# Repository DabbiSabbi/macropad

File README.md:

# My-Macropad
- A macropad that uses F13-19
- Has an RGB light bar.
- Has a display
- Has 6 keys and an rotary encoder

The body is in 3 parts, a lid, base and diffuser, The diffuser is meant to be printed in a clear material such as clear PETG. 

# BOM
| Part | Quantity |
| - | - |
| Seeed XIAO RP2040  | 1 |
| 1N4148 Diodes  | 7 |
| MX-Style switches  | 6 |
| EC11E Rotary encoders | 1 |
| 0.91 inch OLED display    | 1 |
| SK6812 MINI-E LEDs | 6 |
| DSA keycaps | 6 |
| M3x16mm screws | 4 |
| M3x5mx4mm heatset inserts | 4 |

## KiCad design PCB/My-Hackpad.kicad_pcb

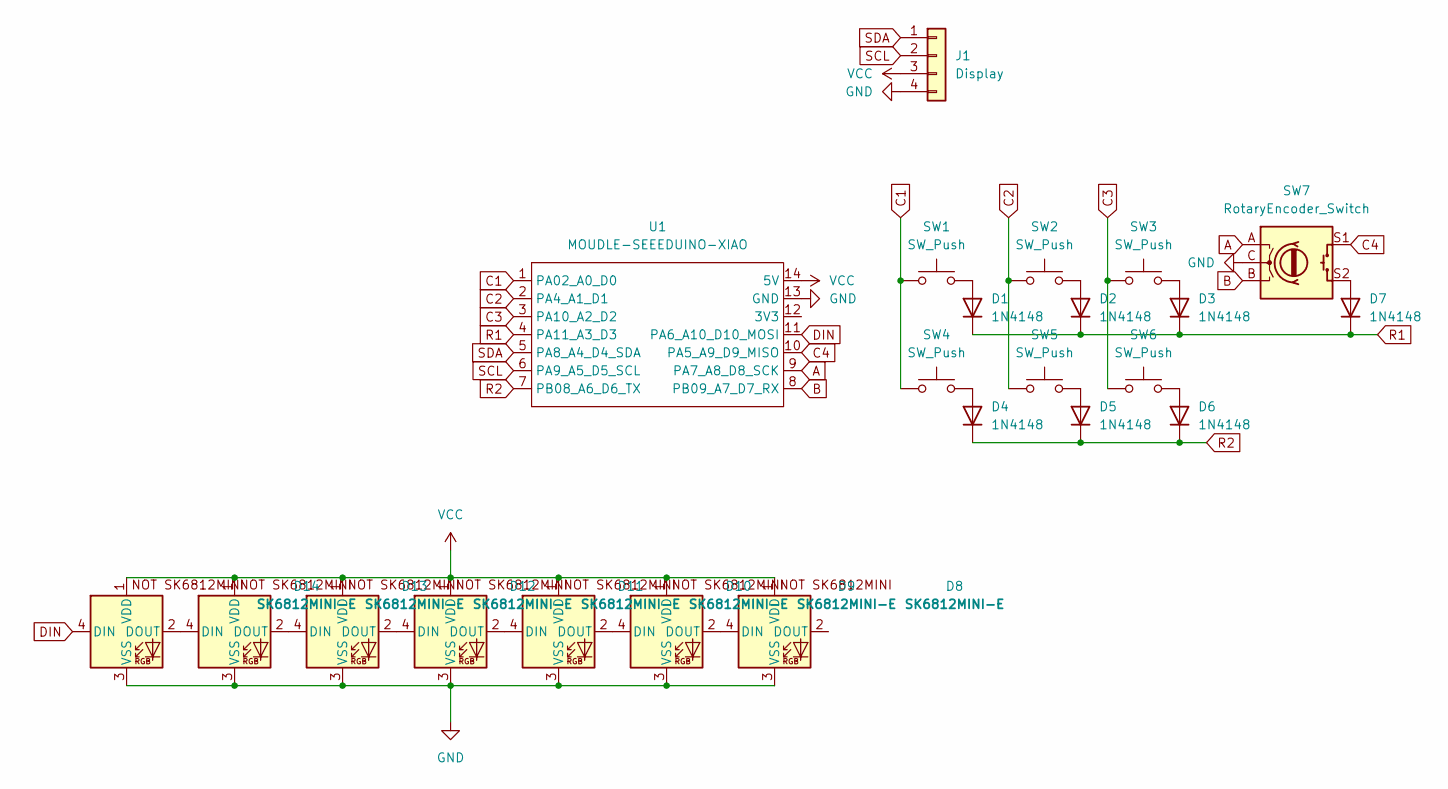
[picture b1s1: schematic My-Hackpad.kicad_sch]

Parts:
D1, D2, D3, D4, D5, D6, D7: 1N4148; D_DO-35_SOD27_P7.62mm_Horizontal
D8: SK6812MINI-E; SK6812MINI-E - 3.2x2.8x1.78mm
D9, D10, D11, D12, D13, D14: SK6812MINI-E; SK6812MINI-E_fixed
J1: Display; PinSocket_1x04_P2.54mm_Horizontal
SW1, SW2, SW3, SW4, SW5, SW6: SW_Push; SW_Cherry_MX_1.00u_PCB
SW7: RotaryEncoder_Switch; RotaryEncoder_Alps_EC11E-Switch_Vertical_H20mm
U1: MOUDLE-SEEEDUINO-XIAO; XIAO-Generic-Hybrid-14P-2.54-21X17.8MM

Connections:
A: SW7.A, U1.9 (PA7_A8_D8_SCK)
B: SW7.B, U1.8 (PB09_A7_D7_RX)
C1: SW1.1, SW4.1, U1.1 (PA02_A0_D0)
C2: SW2.1, SW5.1, U1.2 (PA4_A1_D1)
C3: SW3.1, SW6.1, U1.3 (PA10_A2_D2)
C4: SW7.S1, U1.10 (PA5_A9_D9_MISO)
DIN: D14.4 (DIN), U1.11 (PA6_A10_D10_MOSI)
GND: D8.3 (VSS), D9.3 (VSS), D10.3 (VSS), D11.3 (VSS), D12.3 (VSS), D13.3 (VSS), D14.3 (VSS), J1.4, SW7.C, U1.13 (GND)
unnamed: D1.2 (A), SW1.2
unnamed: D2.2 (A), SW2.2
unnamed: D3.2 (A), SW3.2
unnamed: D4.2 (A), SW4.2
unnamed: D5.2 (A), SW5.2
unnamed: D6.2 (A), SW6.2
unnamed: D7.2 (A), SW7.S2
unnamed: D8.4 (DIN), D9.2 (DOUT)
unnamed: D10.4 (DIN), D11.2 (DOUT)
unnamed: D9.4 (DIN), D10.2 (DOUT)
unnamed: D11.4 (DIN), D12.2 (DOUT)
unnamed: D12.4 (DIN), D13.2 (DOUT)
unnamed: D13.4 (DIN), D14.2 (DOUT)
R1: D1.1 (K), D2.1 (K), D3.1 (K), D7.1 (K), U1.4 (PA11_A3_D3)
R2: D4.1 (K), D5.1 (K), D6.1 (K), U1.7 (PB08_A6_D6_TX)
SCL: J1.2, U1.6 (PA9_A5_D5_SCL)
SDA: J1.1, U1.5 (PA8_A4_D4_SDA)
VCC: D8.1 (VDD), D9.1 (VDD), D10.1 (VDD), D11.1 (VDD), D12.1 (VDD), D13.1 (VDD), D14.1 (VDD), J1.3, U1.14 (5V)

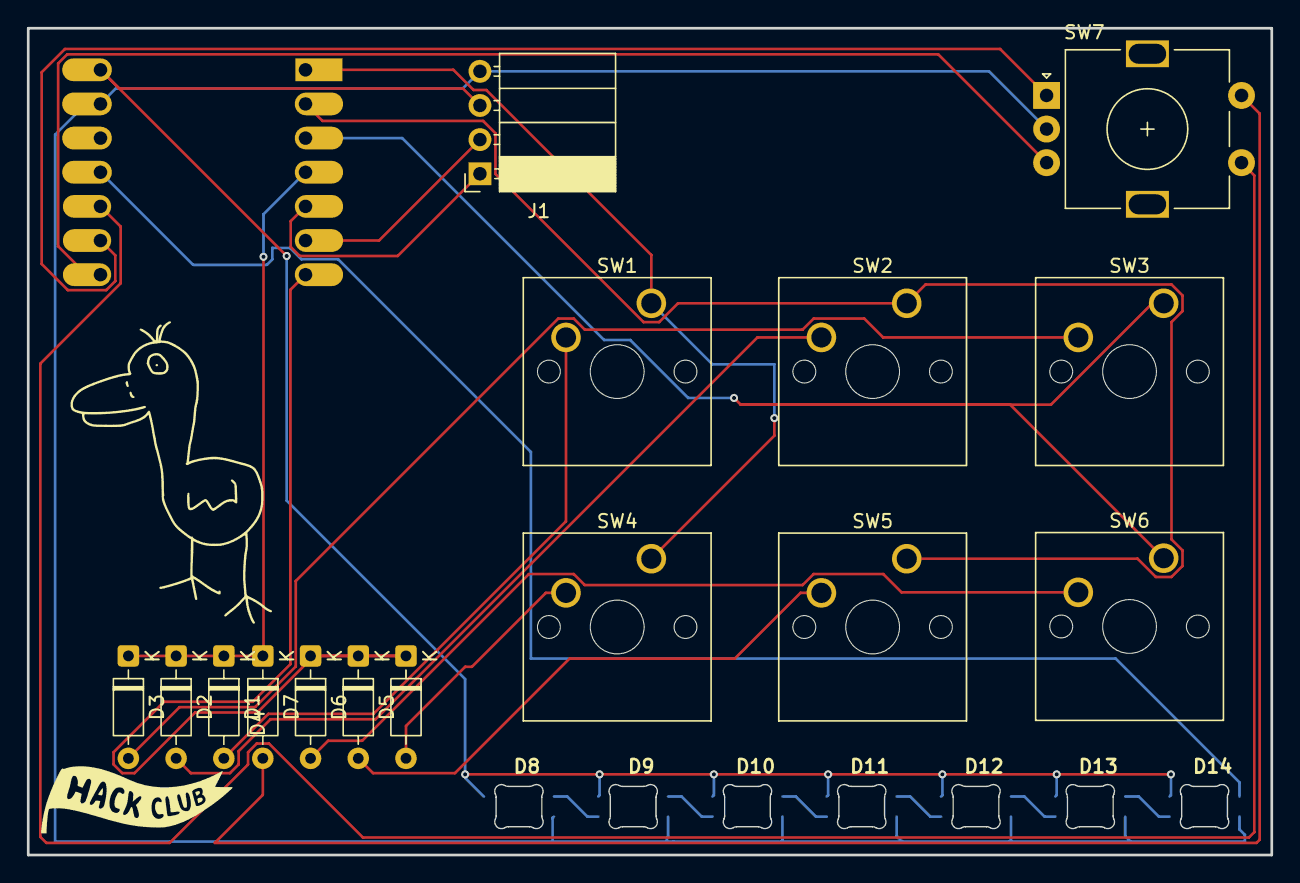
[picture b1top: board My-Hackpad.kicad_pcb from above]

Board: 2 copper layers, 92.5 x 61.5 mm, 23 parts (1 on the bottom side), 26 nets.
